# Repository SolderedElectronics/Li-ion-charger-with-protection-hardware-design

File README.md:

# Li-ion charger with protection Hardware design

## About the product

|  |
| :----------------------------------------------------------: |
|      [Buy Li-ion charger with protection](https://www.solde.red/333014)      |

Lithium batteries are charged differently than regular batteries and devices. You’ll need a li-ion charger like this one to charge them. Integrated with the CC/CV charging technology, it is the simplest way to charge a lithium-ion battery. Protection activated in cases of undervoltage, overvoltage and short circuit, which is enough protection for most batteries.

The board has a USB Type-C connector for power, a JST-type connector for batteries, the charging circuit, a protector, and two status LEDs.

## Repository contents

All Soldered Electronics hardware designed in KiCAD, and repositories are organized in the following way:

- CAD folder - contains KiCAD files (Schematics, Board, Panel Board), sorted by version. Change log lists all changes between versions.
- OUTPUTS - contains useful files, such as Bill of Materials (BOM), PDF of schematics, 3D .step file of the board and gerber files, sorted by version. 
- OUTPUTS -> Compliance - Certificates and useful legal stuff. 

## Want to contribute?

Please feel free to submit a pull request if you have any contributions. We encourage you to submit an issue or pull request if you find a bug. 

## About Soldered

At Soldered, we design and manufacture a wide selection of electronic products to help you turn your ideas into acts and bring you one step closer to your final project. Our products are intented for makers and crafted in-house by our experienced team in Osijek, Croatia. We believe that sharing is a crucial element for improvement and innovation, and we work hard to stay connected with all our makers regardless of their skill or experience level. Therefore, all our products are open-source. Finally, we always have your back. If you face any problem concerning either your shopping experience or your electronics project, our team will help you deal with it, offering efficient customer service and cost-free technical support anytime. Some of those might be useful for you:

- [Web Store](https://www.soldered.com/shop)
- [Tutorials & Projects](https://soldered.com/learn)
- [Community & Technical support](https://soldered.com/community)

## License info

All Soldered open-source hardware (OSH) is under The TAPR Open Hardware License. Read more in the LICENSE file. 

No warranty - all designs in this repository are distributed in the hope that they will be useful, but without any warranty. They are provided "AS IS", therefore without warranty of any kind, either expressed or implied. The entire quality and performance of what you do with the contents of this repository are your responsibility. In no event, Soldered Electronics will be liable for your damages, losses, including any general, special, incidental or consequential damage arising out of the use or inability to use the contents of this repository. 

## Have fun! 
And thank you from your fellow makers at Soldered Electronics.

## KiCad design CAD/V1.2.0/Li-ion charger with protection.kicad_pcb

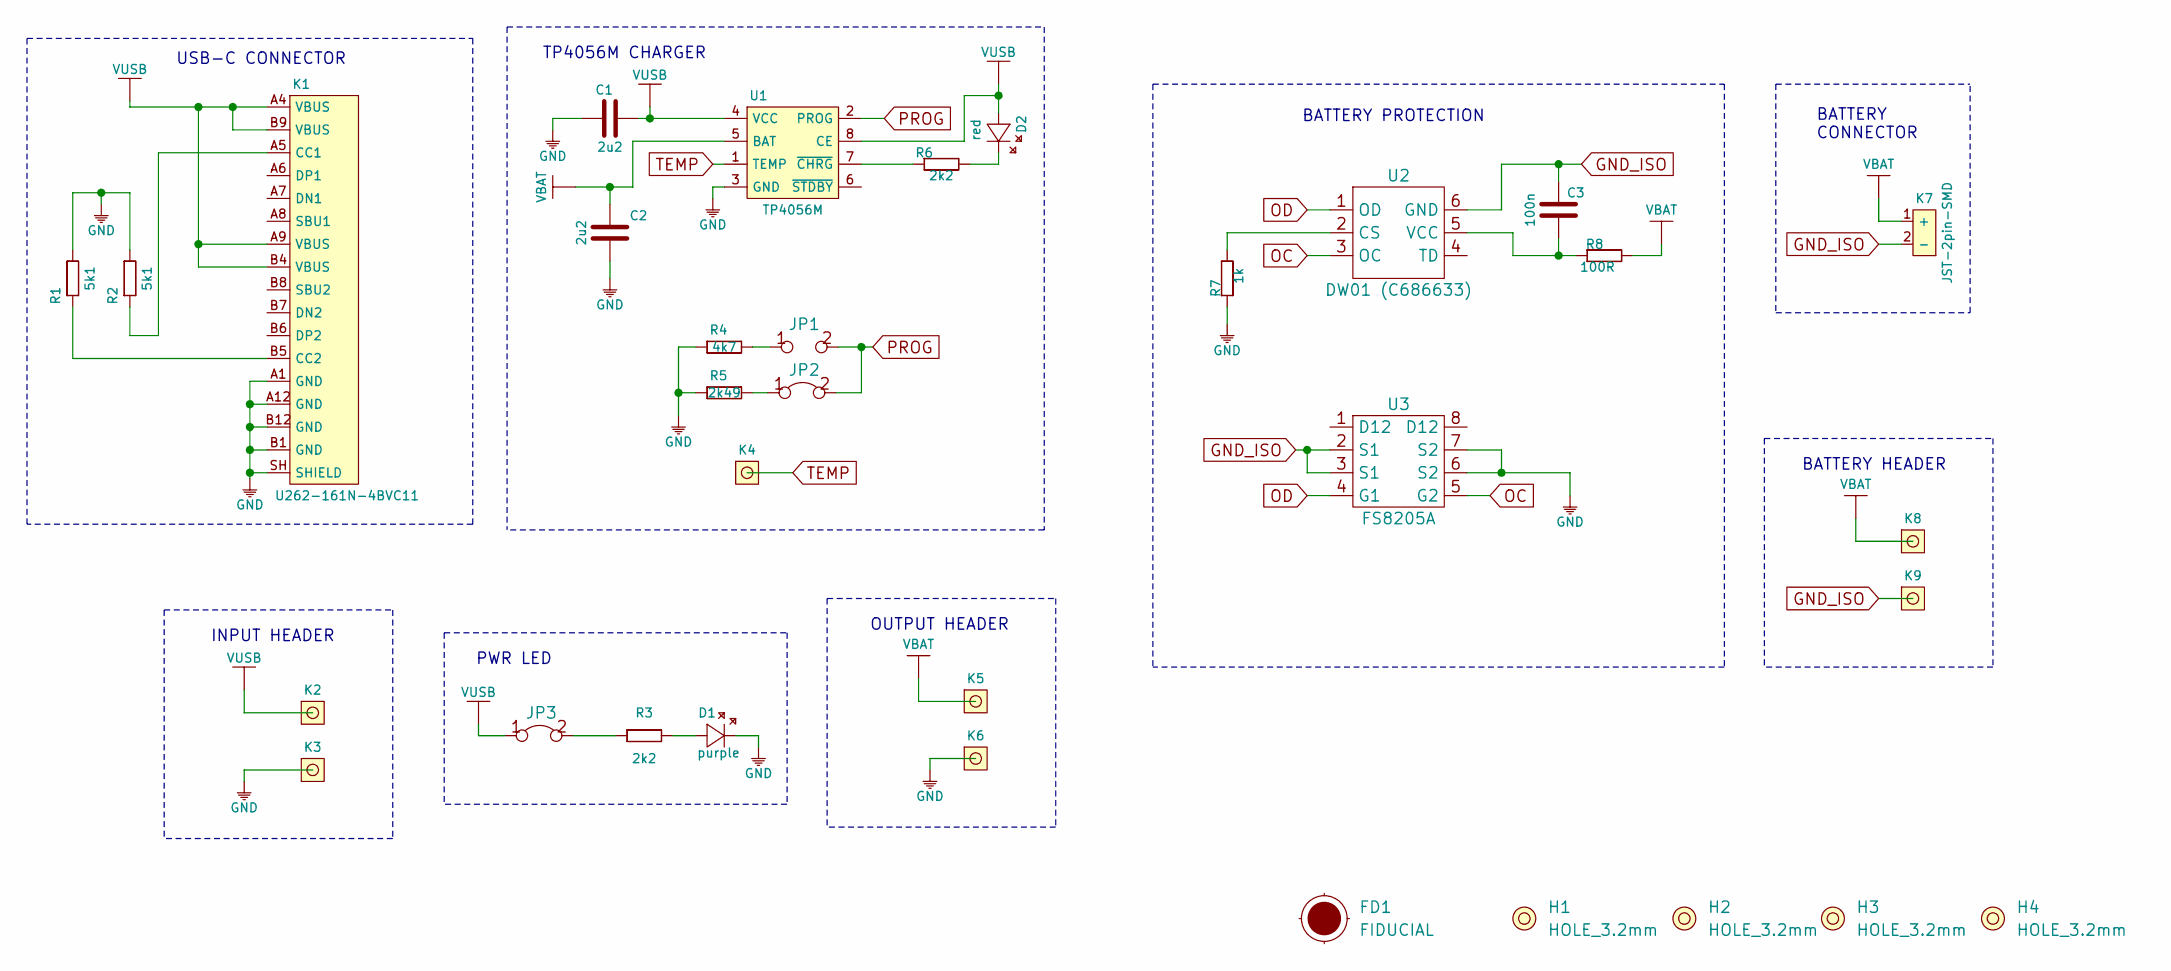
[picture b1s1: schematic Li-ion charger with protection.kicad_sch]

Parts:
C1, C2: 2u2; 0603C
C3: 100n; 0603C
D1: purple; 0402LED
D2: red; 0402LED
FD1: FIDUCIAL; FIDUCIAL_23
H1, H2, H3, H4: HOLE_3.2mm
JP1: SMD_JUMPER
JP2: SMD-JUMPER-CONNECTED; SMD_JUMPER_CONNECTED
JP3: SMD-JUMPER-CONNECTED_TRACE_SLODERMASK
K1: U262-161N-4BVC11
K2, K3, K4, K5, K6, K8, K9: HEADER_MALE_1X1
K7: JST-2pin-SMD
R1, R2: 5k1; 0603R
R3, R6: 2k2; 0402R
R4: 4k7; 0603R
R5: 2k49; 0603R
R7: 1k; 0603R
R8: 100R; 0603R
U1: TP4056M; TP4056M-MSOP8
U2: DW01 (C686633); Sot23-6
U3: FS8205A; TSSOP8

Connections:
GND: C1.1, C2.1, D1.2 (K), K1.A1 (GND), K1.A12 (GND), K1.B1 (GND), K1.B12 (GND), K1.SH (SHIELD), K3.1, K6.1, R1.2, R2.2, R4.1, R5.1, R7.1, U1.3 (GND), U3.6 (S2), U3.7 (S2)
GND_ISO: C3.2, K7.2 (-), K9.1, U2.6 (GND), U3.2 (S1), U3.3 (S1)
unnamed: C3.1, R8.1, U2.5 (VCC)
unnamed: D1.1 (A), R3.2
unnamed: D2.2 (K), R6.2
unnamed: JP1.1, R4.2
unnamed: JP2.1, R5.2
unnamed: JP3.2, R3.1
unnamed: K1.A5 (CC1), R2.1
unnamed: K1.B5 (CC2), R1.1
unnamed: R6.1, U1.7 (~CHRG)
unnamed: R7.2, U2.2 (CS)
OC: U2.3 (OC), U3.5 (G2)
OD: U2.1 (OD), U3.4 (G1)
PROG: JP1.2, JP2.2, U1.2 (PROG)
TEMP: K4.1, U1.1 (TEMP)
VBAT: C2.2, K5.1, K7.1 (+), K8.1, R8.2, U1.5 (BAT)
VUSB: C1.2, D2.1 (A), JP3.1, K1.A4 (VBUS), K1.A9 (VBUS), K1.B4 (VBUS), K1.B9 (VBUS), K2.1, U1.4 (VCC), U1.8 (CE)

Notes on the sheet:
BATTERY PROTECTION
BATTERY CONNECTOR
PWR LED
USB-C CONNECTOR
BATTERY HEADER
OUTPUT HEADER
INPUT HEADER
TP4056M CHARGER

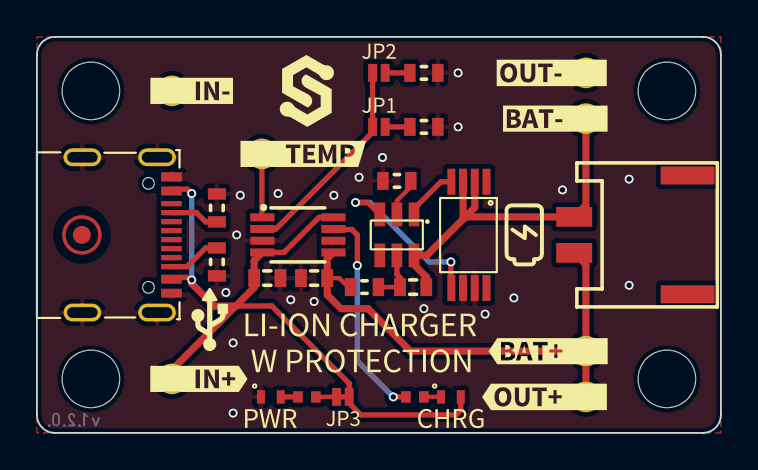
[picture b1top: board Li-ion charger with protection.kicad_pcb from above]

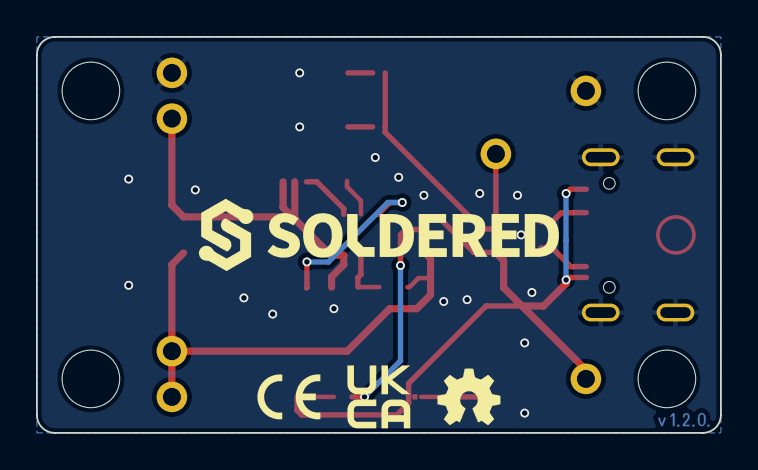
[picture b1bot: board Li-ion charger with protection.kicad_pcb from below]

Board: 2 copper layers, 38.0 x 22.0 mm, 47 parts (7 on the bottom side), 18 nets.

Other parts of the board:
kibuzzard-669504AA: G***; kibuzzard-669504AA
kibuzzard-669504B1: G***; kibuzzard-669504B1
kibuzzard-669504CA: G***; kibuzzard-669504CA
kibuzzard-669504E0: G***; kibuzzard-669504E0
kibuzzard-669504EC: G***; kibuzzard-669504EC
kibuzzard-6695049F: G***; kibuzzard-6695049F
kibuzzard-66950404: G***; kibuzzard-66950404
kibuzzard-66950417: G***; kibuzzard-66950417
kibuzzard-66950472: G***; kibuzzard-66950472
kibuzzard-66950480: G***; kibuzzard-66950480
kibuzzard-66950492: G***; kibuzzard-66950492
kibuzzard-66950503: G***; kibuzzard-66950503
kibuzzard-66950510: G***; kibuzzard-66950510
kibuzzard-66950525: G***; kibuzzard-66950525

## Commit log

2022-08-06 Updating open source files.
